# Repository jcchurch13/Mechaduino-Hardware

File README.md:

Engineers use servo motors to achieve the precision motion required in applications such as robotics, automation, and CNC manufacturing. Like RC servos, industrial servos actively correct for external disturbances. Unlike RC servos, industrial servos can provide very accurate motion, and often support advanced motion control modes. Unfortunately the cost of industrial servos is prohibitive to the individual maker (thousands of dollars per motor).

We've been developing an affordable open-source industrial servo motor, opening the door to sophisticated mechatronics applications. Our design leverages the low cost of mass produced stepper motors. We are able to achieve very high resolution via 14b encoder feedback (after calibration routine!).

## Project Goals

 - Position, velocity, torque loops
 - Step & direction inputs for drop-in compatibility with stepper motors / step stick
 - I2c, serial inputs
 - Customizable/open source with access to internal variables
 - Transparent and user-definable control algorithms (commercial servos often lack this)
 - Arduino compatible with easy to use interface
 - High resolution pointing (sub 0.1 degree)
 - Low cost (should not be a huge leap from stepper + stepstick cost)
 - Serial interfaces for inter-motor communication
 - On-board processor allows for stand alone for simple applications
 - Adjustable commutation profiles
 - PID auto tuning
 - Anti-cogging capable
 - Open to customization. Outside of our firmware, we see Mechaduino as a very useful hardware package. If you would like to use the stepper motor in open loop mode w/ encoder to verify location, you can do that.

## Strategy

An industrial servo motor can be broken down into four main components (below). First we looked at each of these components and tried to piece together an affordable breadboard-level prototype. After some experimentation, we were able to distill out a working lineup of components. From there, we've been iterating on our design, working out all the kinks, and tuning the control loops. It's starting to come together!

...Back to those four main components:

1. The actual motor, usually of the brushless dc variety. When you look at industrial servo motors, a big chunk of the cost is the motor itself. They are often custom built, or at least built in limited quantities, which means $$$. Watt for watt, I'd guess that a mass produced NEMA 17 or NEMA 23 stepper motor is between a tenth and a hundredth the cost of the BDC motors used in industrial servos. Although their design is optimized for "stepping," stepper motors are really just 50-pole brushless dc motors. They can be controlled exactly like a more traditional 3 phase BDC motor with more poles. So that's the plan. It's working!

2. A sensor for feedback, usually an encoder. Optical encoders are pretty standard, but get quite pricey if you want high resolution and/or absolute position information. We were intrigued by some of the cheap, high resolution magnetic encoders offered by vendors like AMS. It turns out that although they claim 12 and 14 bit resolutions (that's 0.09 and 0.02 degrees respectively), they suffer from non-linearities on the order of a degree or so! However, we found that this non-linearity is very repeatable, and we were able to develop a quick, self contained (on motor) calibration routine that restores resolution to better than 0.1 degrees. (More on this later. This was a significant design effort and is worthy of its own build log!)

3. Drive circuitry/power electronics to excite the motor windings. Many industrial servos use discrete H bridges. Each phase requires it's own H bridge ( for a two phase motor... half bridges for each in a three phase motor), which consists of at least 4 if not 8 (...including freewheeling diodes) discrete switching devices. Throw in gate drive circuitry, and things start to get expensive. We hoped to find a single-chip, integrated solution that would allow for current feedback, and we found just that in the A4954 dual full bridge PWM driver.

4. Control Electronics. Usually a microcontroller or FPGA. Early on, we decided that Arduino compatibility was a must in order to make the firmware as accessible as possible. We chose to use a SAMD21 ARM M0+ (Arduino Zero compatible) processor to balance cost and performance. Our breadboard prototype system verified that this processor was more than capable of executing the necessary algorithms.

### Application Examples:

 - [Fine, closed loop positioning for 3D printers](https://www.youtube.com/watch?v=T1HIWAiMrfY)
 - Fine pointing for optics (laser, telescope, camera gimbal)
 - Velocity loop for a record player
 - Force feedback/impedance control for robotics
 - Force feedback for gaming controllers
 - Adjustable mechanical impedance: virtual spring,mass,damper
 - Electrical gearing between two axes on a cnc machine, etc.
 - Haptics
 - Tele-operation
 - Gravity-cancellation (counter the gravitational torques on a robotic arm for example)
 - Load detection and characterization (simple case: use as a scale!)
 - Paper towel/tp dispenser
 - Variable load (brake)
 - Variable load (generator)
 - After market valve control (automate a garden hose, etc)

### Other Advantages:

- Finer resolution than stepper motors (0.02 degrees)
- True closed loop for disturbance rejection
- Lower power consumption: only uses power to fight disturbances. This in turn means higher peak torque.
- Absolute position control (not incremental). No need to home on power-on.

## License

All Mechaduino related materials are released under the
[Creative Commons Attribution Share-Alike 4.0 License](https://creativecommons.org/licenses/by-sa/4.0/)

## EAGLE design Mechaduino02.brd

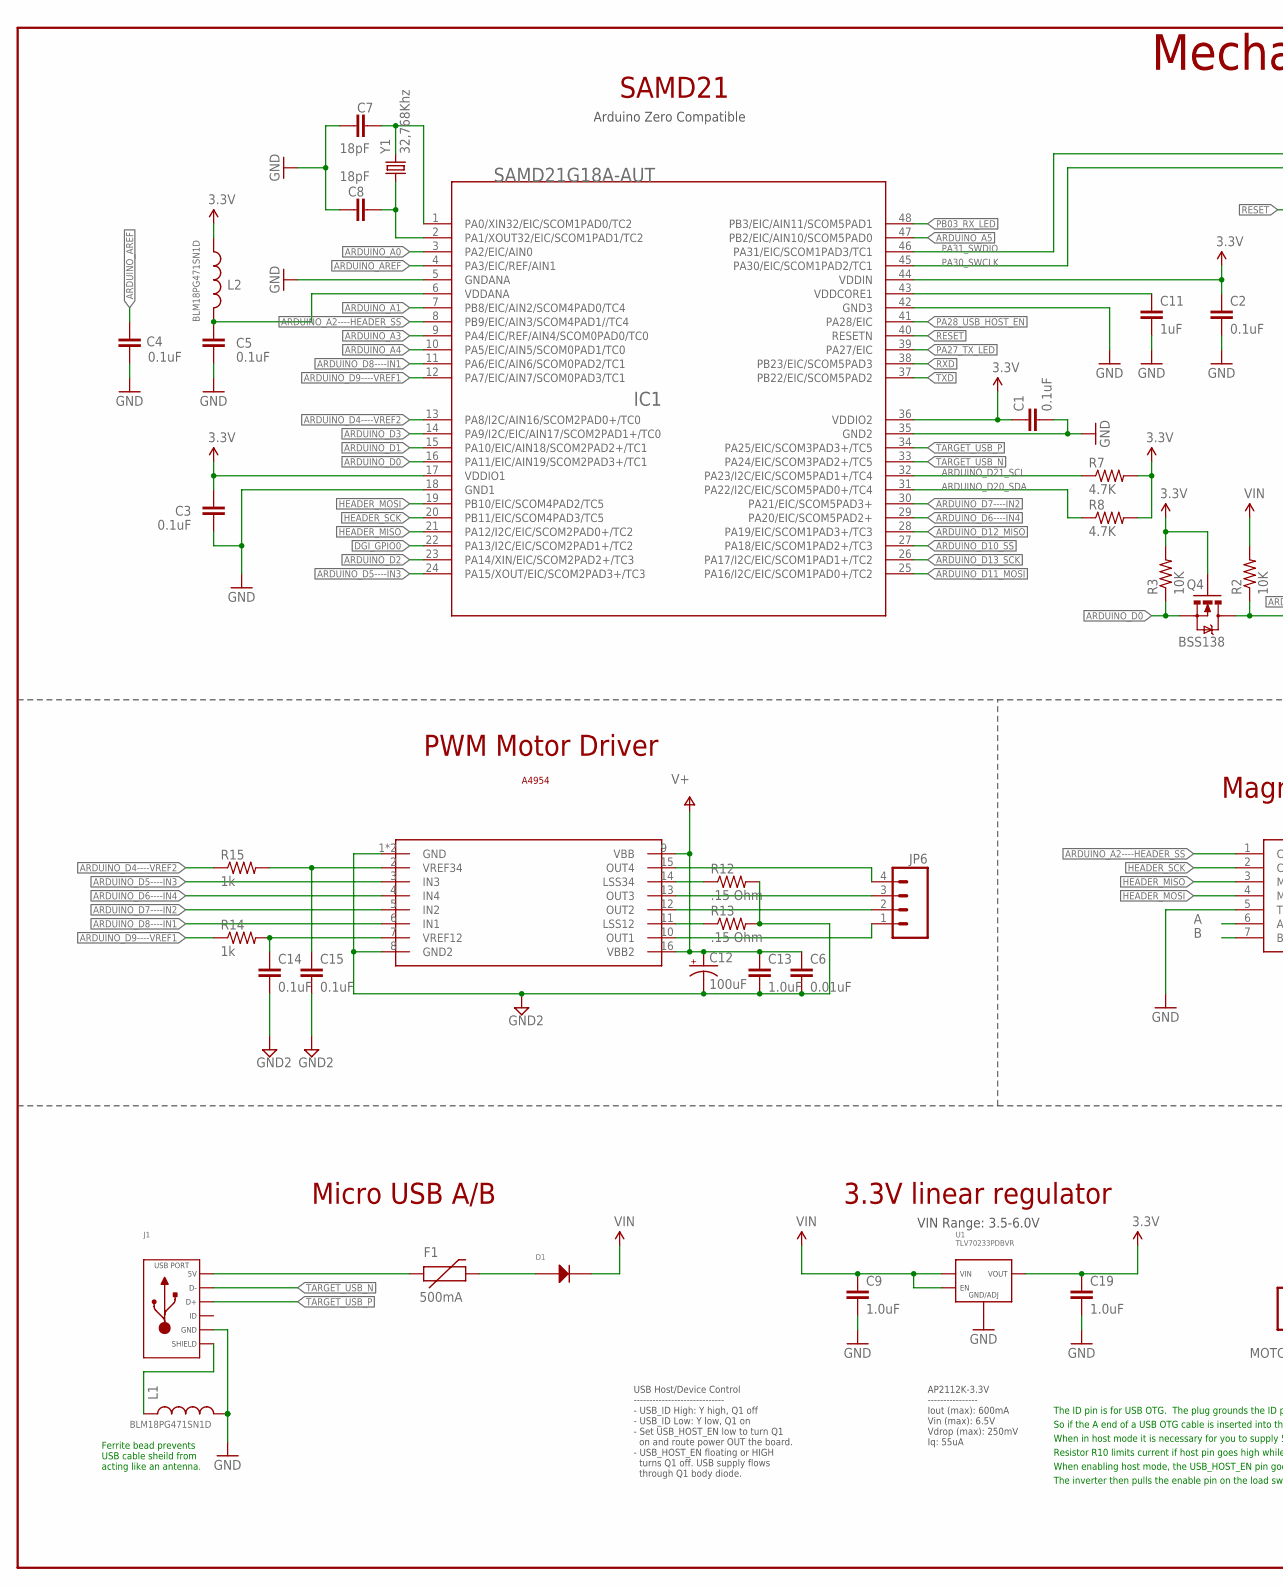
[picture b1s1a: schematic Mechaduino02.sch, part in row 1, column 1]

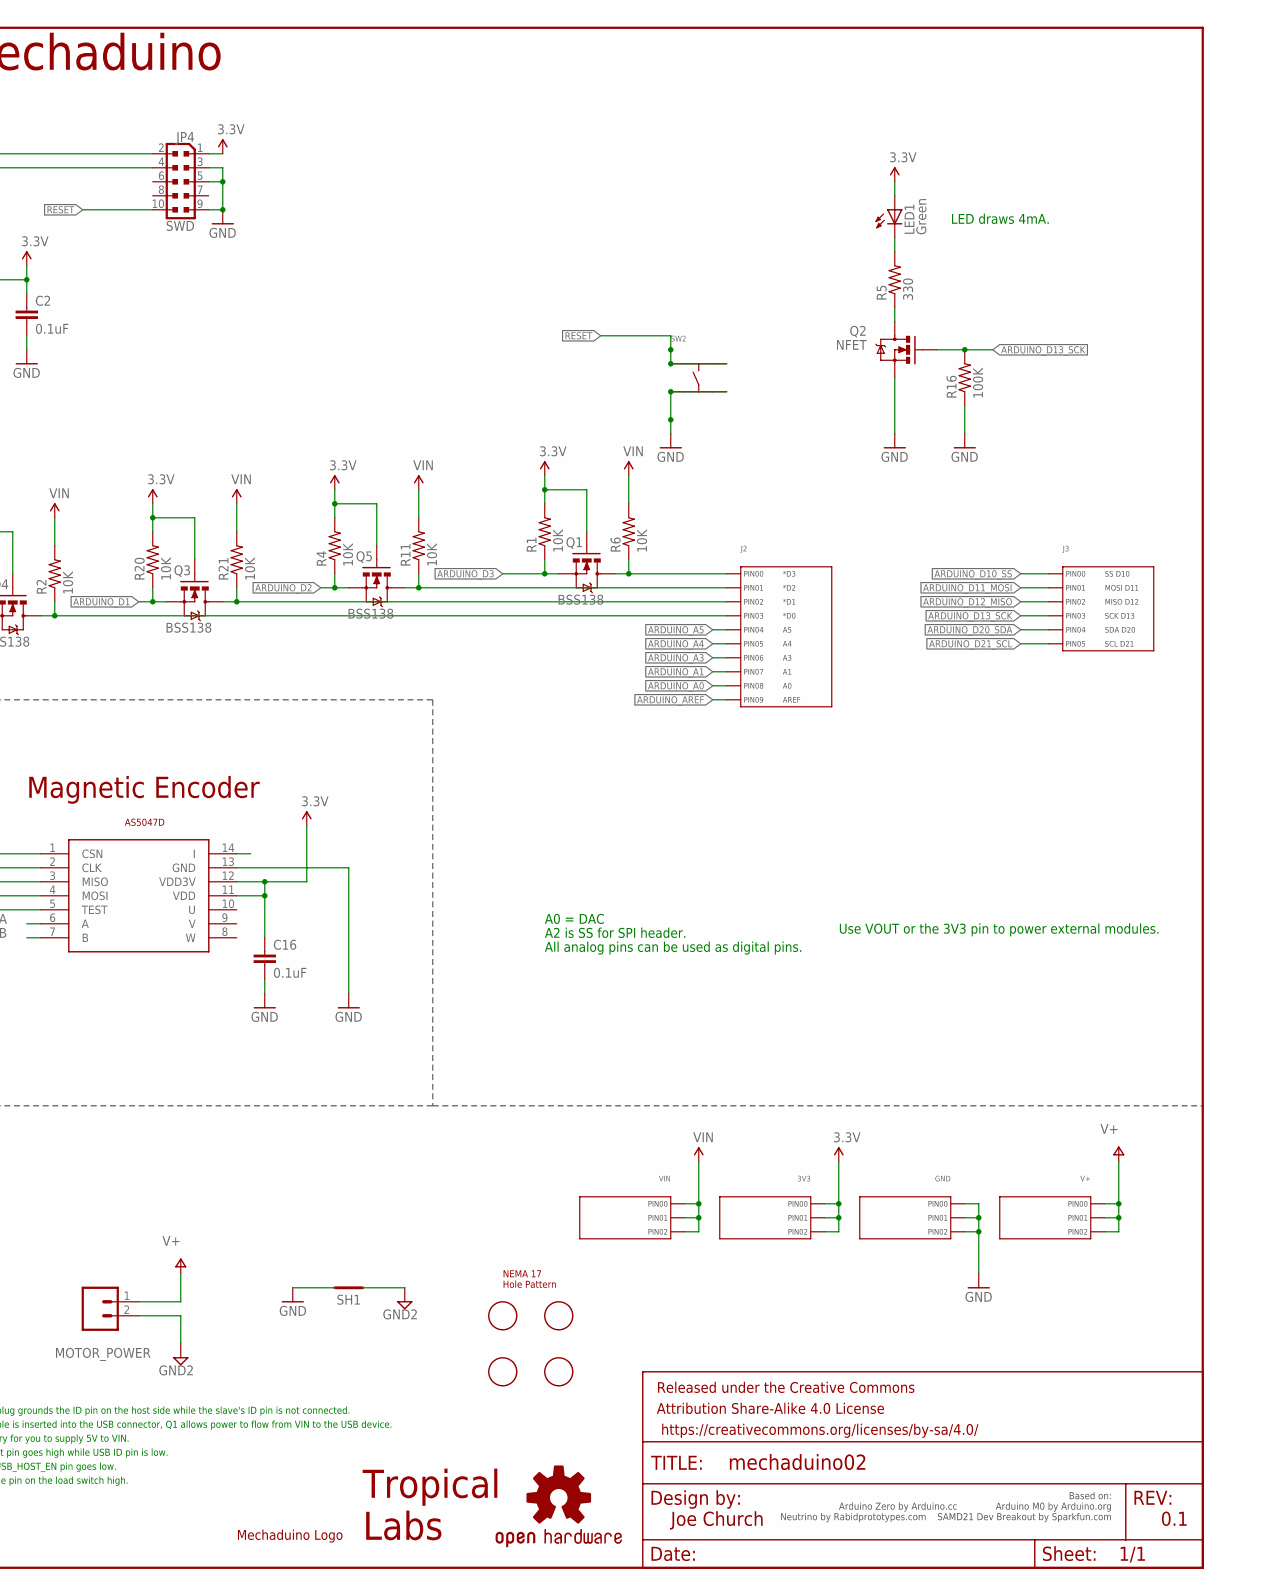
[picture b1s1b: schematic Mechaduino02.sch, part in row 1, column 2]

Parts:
3V3: HEADER_01X03_PTH_2.54MM; PTH_2.54MM_01X03
C1, C2, C3, C4, C5, C14, C15, C16: 0.1uF; 0402-CAP
C6: 0.01uF; 0603-CAP
C7, C8: 18pF; 0603-CAP
C9, C19: 1.0uF; 0402-CAP
C11: 1uF; 0402-CAP
C12: 100uF; PANASONIC_D
C13: 1.0uF; 0603-CAP
D1: DIODE_SOD-123; SOD-123
F1: 500mA; PTC-1206
FRAME1: FRAME-LEDGER; CREATIVE_COMMONS
GND: HEADER_01X03_PTH_2.54MM; PTH_2.54MM_01X03
IC1: SAMD21G18A-AUT; INTEGRATEDCIRCUITS_TQFP48-7X7
J1: USB_MICRO_RIGHT; MICROUSB-RIGHT
J2: HEADER_01X10_PTH_2.54MM; PTH_2.54MM_01X10
J3: HEADER_01X06_PTH_2.54MM; PTH_2.54MM_01X06
JP4: SWD; CONNETTORI_PINHEAD-2X5-P127
JP6: M04PTH; 1X04
L1, L2: BLM18PG471SN1D; 0603-TDK
LED1: Green; CHIPLED_0805
LOGO4: OSHW-LOGOMOD; OSHW_LOGO_COPPER_MOD
MOTOR_POWER: M025MM; SCREWTERMINAL-5MM-2
Q1, Q3, Q4, Q5: BSS138; SOT23-3
Q2: NFET; SOT323
R1, R2, R3, R4, R6, R11, R20, R21: 10K; R0402-VISHAY
R5: 330; R0402-VISHAY
R7, R8: 4.7K; R0402-VISHAY
R12, R13: .15 Ohm; R1206
R14, R15: 1k; R0402-VISHAY
R16: 100K; R0402-VISHAY
SH1: SHORT-HA5; SHORT_ALL-50
SW2: TACT_4.2MM; TACT4.2MM
U1: TLV70233PDBVR; SOT-23-5
U$1: AVAGO_DRIVERTHERM; TSSOP16_THERM
U$2: NEMA17_HOLE_PATTERNNEW; NEMA17_HOLE_PATTERN_2
U$3: TROPICAL_LABS_LOGO_1LOGO3; LOGO3
U$4: AS5047D; TSSOP14
U$5: MECHADUINO_LOGO
V+: HEADER_01X03_PTH_2.54MM; PTH_2.54MM_01X03
VIN: HEADER_01X03_PTH_2.54MM; PTH_2.54MM_01X03
Y1: 32,768Khz; CRYSTAL-SMD-2.0X1.2

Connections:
3.3V: 3V3.P$1 (PIN0), 3V3.P$2 (PIN1), 3V3.P$3 (PIN2), C1.1, C2.1, C3.2, C16.1, C19.1, IC1.17 (VDDIO1), IC1.36 (VDDIO2), IC1.44 (VDDIN), JP4.1, L2.1, LED1.A, Q1.1 (G), Q3.1 (G), Q4.1 (G), Q5.1 (G), R1.2, R3.2, R4.2, R7.2, R8.2, R20.2, U1.P$5 (VOUT), U$4.11 (VDD), U$4.12 (VDD3V)
A: U$4.6 (A)
ARDUINO_A0: IC1.3 (PA2/EIC/AIN0), J2.P$9 (PIN8)
ARDUINO_A1: IC1.7 (PB8/EIC/AIN2/SCOM4PAD0/TC4), J2.P$8 (PIN7)
ARDUINO_A2----HEADER_SS: IC1.8 (PB9/EIC/AIN3/SCOM4PAD1//TC4), U$4.1 (CSN)
ARDUINO_A3: IC1.9 (PA4/EIC/REF/AIN4/SCOM0PAD0/TC0), J2.P$7 (PIN6)
ARDUINO_A4: IC1.10 (PA5/EIC/AIN5/SCOM0PAD1/TC0), J2.P$6 (PIN5)
ARDUINO_A5: IC1.47 (PB2/EIC/AIN10/SCOM5PAD0), J2.P$5 (PIN4)
ARDUINO_AREF: C4.1, IC1.4 (PA3/EIC/REF/AIN1), J2.P$10 (PIN9)
ARDUINO_D0: IC1.16 (PA11/EIC/AIN19/SCOM2PAD3+/TC1), Q4.2 (S), R3.1
ARDUINO_D1: IC1.15 (PA10/EIC/AIN18/SCOM2PAD2+/TC1), Q3.2 (S), R20.1
ARDUINO_D2: IC1.23 (PA14/XIN/EIC/SCOM2PAD2+/TC3), Q5.2 (S), R4.1
ARDUINO_D3: IC1.14 (PA9/I2C/EIC/AIN17/SCOM2PAD1+/TC0), Q1.2 (S), R1.1
ARDUINO_D4----VREF2: IC1.13 (PA8/I2C/AIN16/SCOM2PAD0+/TC0), R15.1
ARDUINO_D5----IN3: IC1.24 (PA15/XOUT/EIC/SCOM2PAD3+/TC3), U$1.3 (IN3)
ARDUINO_D6----IN4: IC1.29 (PA20/EIC/SCOM5PAD2+), U$1.4 (IN4)
ARDUINO_D7----IN2: IC1.30 (PA21/EIC/SCOM5PAD3+), U$1.5 (IN2)
ARDUINO_D8----IN1: IC1.11 (PA6/EIC/AIN6/SCOM0PAD2/TC1), U$1.6 (IN1)
ARDUINO_D9----VREF1: IC1.12 (PA7/EIC/AIN7/SCOM0PAD3/TC1), R14.1
ARDUINO_D10_SS: IC1.27 (PA18/EIC/SCOM1PAD2+/TC3), J3.P$1 (PIN0)
ARDUINO_D11_MOSI: IC1.25 (PA16/I2C/EIC/SCOM1PAD0+/TC2), J3.P$2 (PIN1)
ARDUINO_D12_MISO: IC1.28 (PA19/EIC/SCOM1PAD3+/TC3), J3.P$3 (PIN2)
ARDUINO_D13_SCK: IC1.26 (PA17/I2C/EIC/SCOM1PAD1+/TC2), J3.P$4 (PIN3), Q2.1 (G), R16.2
ARDUINO_D20_SDA: IC1.31 (PA22/I2C/EIC/SCOM5PAD0+/TC4), J3.P$5 (PIN4), R8.1
ARDUINO_D21_SCL: IC1.32 (PA23/I2C/EIC/SCOM5PAD1+/TC4), J3.P$6 (PIN5), R7.1
B: U$4.7 (B)
DGI_GPIO0: IC1.22 (PA13/I2C/EIC/SCOM2PAD1+/TC2)
GND: C1.2, C2.2, C3.1, C4.2, C5.2, C7.1, C8.1, C9.2, C11.2, C16.2, C19.2, GND.P$1 (PIN0), GND.P$2 (PIN1), GND.P$3 (PIN2), IC1.5 (GNDANA), IC1.18 (GND1), IC1.35 (GND2), IC1.42 (GND3), J1.5 (GND), JP4.3, JP4.5, JP4.9, L1.2, Q2.2 (S), R16.1, SH1.2, SW2.P$3, SW2.P$4, U1.P$2 (GND/ADJ), U$4.5 (TEST), U$4.13 (GND)
GND2: C6.2, C12.-, C13.2, C14.2, C15.2, MOTOR_POWER.2, R12.2, R13.2, SH1.1, U$1.1 (GND), U$1.8 (GND2), U$1.P$1 (GND)
HEADER_MISO: IC1.21 (PA12/I2C/EIC/SCOM2PAD0+/TC2), U$4.3 (MISO)
HEADER_MOSI: IC1.19 (PB10/EIC/SCOM4PAD2/TC5), U$4.4 (MOSI)
HEADER_SCK: IC1.20 (PB11/EIC/SCOM4PAD3/TC5), U$4.2 (CLK)
HV1: J2.P$3 (PIN2), Q3.3 (D), R21.1
HV2: J2.P$4 (PIN3), Q4.3 (D), R2.1
HV3: J2.P$2 (PIN1), Q5.3 (D), R11.1
HV4: J2.P$1 (PIN0), Q1.3 (D), R6.1
I: U$4.14 (I)
unnamed: LED1.C, R5.2
unnamed: R12.1, U$1.14 (LSS34)
unnamed: Q2.3 (D), R5.1
unnamed: R13.1, U$1.11 (LSS12)
unnamed: C15.1, R15.2, U$1.2 (VREF34)
unnamed: JP6.4, U$1.15 (OUT4)
unnamed: JP6.1, U$1.10 (OUT1)
unnamed: JP6.2, U$1.12 (OUT2)
unnamed: JP6.3, U$1.13 (OUT3)
unnamed: C14.1, R14.2, U$1.7 (VREF12)
unnamed: D1.ANODE, F1.2
unnamed: F1.1, J1.1 (5V)
PA00_XIN32: C7.2, IC1.1 (PA0/XIN32/EIC/SCOM1PAD0/TC2), Y1.2
PA01_XOUT32: C8.2, IC1.2 (PA1/XOUT32/EIC/SCOM1PAD1/TC2), Y1.1
PA27_TX_LED: IC1.39 (PA27/EIC)
PA28_USB_HOST_EN: IC1.41 (PA28/EIC)
PA30_SWCLK: IC1.45 (PA30/EIC/SCOM1PAD2/TC1), JP4.4
PA31_SWDIO: IC1.46 (PA31/EIC/SCOM1PAD3/TC1), JP4.2
PB03_RX_LED: IC1.48 (PB3/EIC/AIN11/SCOM5PAD1)
RESET: IC1.40 (RESETN), JP4.10, SW2.P$1, SW2.P$2
RXD: IC1.38 (PB23/EIC/SCOM5PAD3)
SHIELD: J1.S1 (SLD), J1.S2 (SLD), J1.S3 (SLD), J1.S4 (SLD), J1.S5 (SLD), J1.S6 (SLD), J1.S7 (SLD), J1.S8 (SLD), L1.1
TARGET_USB_N: IC1.33 (PA24/EIC/SCOM3PAD2+/TC5), J1.2 (D-)
TARGET_USB_P: IC1.34 (PA25/EIC/SCOM3PAD3+/TC5), J1.3 (D+)
TXD: IC1.37 (PB22/EIC/SCOM5PAD2)
V+: C6.1, C12.+, C13.1, MOTOR_POWER.1, U$1.9 (VBB), U$1.16 (VBB2), V+.P$1 (PIN0), V+.P$2 (PIN1), V+.P$3 (PIN2)
VDDANA: C5.1, IC1.6 (VDDANA), L2.2
VDDCORE: C11.1, IC1.43 (VDDCORE1)
VIN: C9.1, D1.CATHODE, R2.2, R6.2, R11.2, R21.2, U1.P$1 (VIN), U1.P$3 (EN), VIN.P$1 (PIN0), VIN.P$2 (PIN1), VIN.P$3 (PIN2)

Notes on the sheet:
A0 = DAC
All analog pins can be used as digital pins.
LED draws 4mA.
A2 is SS for SPI header.
Use VOUT or the 3V3 pin to power external modules.
Ferrite bead prevents USB cable sheild from acting like an antenna.
The ID pin is for USB OTG. The plug grounds the ID pin on the host side while the slave's ID pin is not connected.
So if the A end of a USB OTG cable is inserted into the USB connector, Q1 allows power to flow from VIN to the USB device.
3.3V linear regulator
When in host mode it is necessary for you to supply 5V to VIN.
When enabling host mode, the USB_HOST_EN pin goes low.
Resistor R10 limits current if host pin goes high while USB ID pin is low.
The inverter then pulls the enable pin on the load switch high.
Magnetic Encoder
SAMD21
PWM Motor Driver
VIN Range: 3.5-6.0V
AP2112K-3.3V ---------------- Iout (max): 600mA Vin (max): 6.5V Vdrop (max): 250mV Iq: 55uA
USB Host/Device Control ----------------------------- - USB_ID High: Y high, Q1 off - USB_ID Low: Y low, Q1 on - Set USB_HOST_EN low to turn Q1 on and route power OUT the board. - USB_HOST_EN floating or HIGH turns Q1 off. USB supply flows through Q1 body diode.
A4954
Micro USB A/B
Joe Church
Based on: Arduino Zero by Arduino.cc Arduino M0 by Arduino.org Neutrino by Rabidprototypes.com SAMD21 Dev Breakout by Sparkfun.com
0.1
Arduino Zero Compatible
Mechaduino

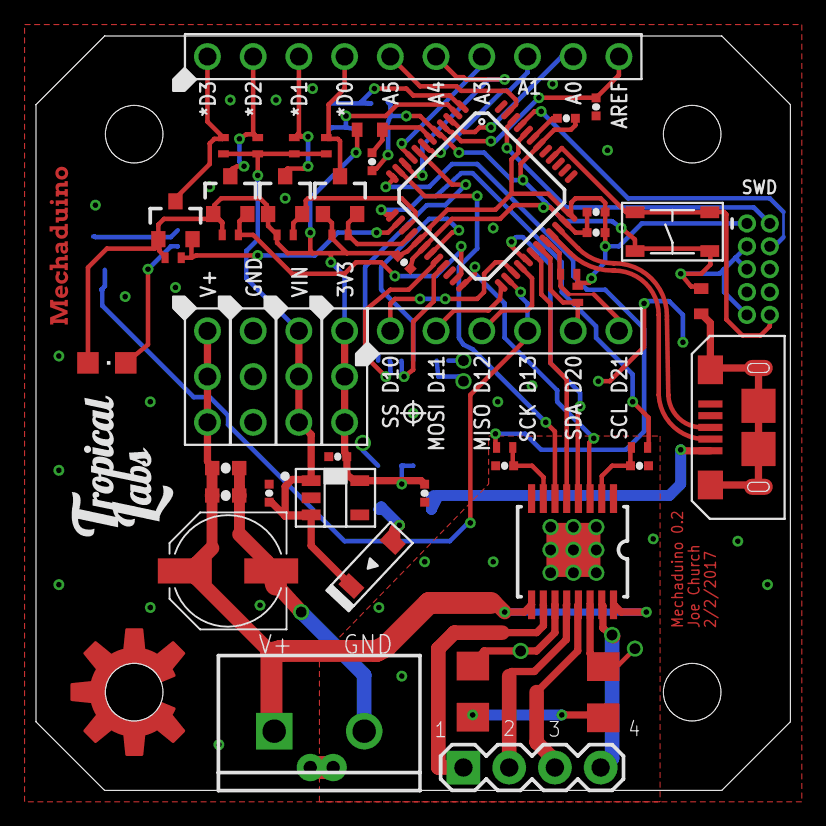
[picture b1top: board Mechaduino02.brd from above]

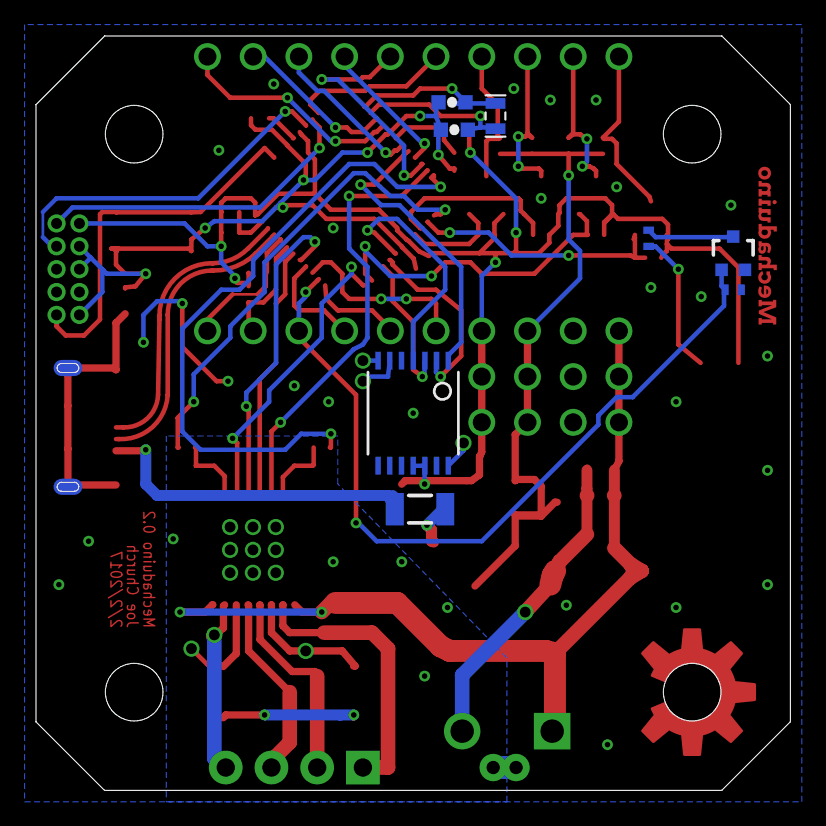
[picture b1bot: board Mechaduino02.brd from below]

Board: 2 copper layers, 41.9 x 41.9 mm, 64 parts (8 on the bottom side), 57 nets.

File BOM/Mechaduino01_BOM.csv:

Qty	Value	Device	Package	Parts	Description											
1	DIODESOD-523	SOD-523	D1	Diode												
4	HEADER_01X03_PTH_2.54MM	PTH_2.54MM_01X03	3V3	GND	V+	VIN	Library:	MF_Connectors								
1	HEADER_01X06_PTH_2.54MM	PTH_2.54MM_01X06	J3	Library:	MF_Connectors											
1	HEADER_01X10_PTH_2.54MM	PTH_2.54MM_01X10	J2	Library:	MF_Connectors											
1	M025MM	SCREWTERMINAL-5MM-2	MOTOR_POWER	"Standard 2-pin 0.1"" header. Use with"												
1	M04PTH	1X04	JP6	Header	4											
1	TACT_4.2MM	TACT4.2MM	SW2	Library:	MF_Switches											
1	USB_MICRO_RIGHT	MICROUSB-RIGHT	J1	Library:	MF_Connectors											
2	0.15	Ohm	R-US_R1206	R1206	R12	R13	RESISTOR	American	symbol							
1	0.01uF	CAP0402	0402-CAP	C6	Capacitor											
10	0.1uF	CAP0402	0402-CAP	C1	C2	C3	C4	C5	C9	C14	C15	C16	C19	Capacitor		
1	1.0uF	CAP0603	0603-CAP	C13	Capacitor											
2	10.0uF	CAP0402	0805-CAP	C10	C18	Capacitor										
2	100K	R-US_R0402-VISHAY	R0402-VISHAY	R1	R9	RESISTOR	American	symbol								
1	100k	R-US_R0402-VISHAY	R0402-VISHAY	R16	RESISTOR	American	symbol									
1	100uF	CAP_POLD	PANASONIC_D	C12	Capacitor	Polarized										
4	10K	R-US_R0402-VISHAY	R0402-VISHAY	R2	R3	R20	R21	RESISTOR	American	symbol						
2	1k	R-US_R0402-VISHAY	R0402-VISHAY	R14	R15	RESISTOR	American	symbol								
2	1uF	CAP0402	0402-CAP	C11	C17	Capacitor										
1	2.5A/30V	MOSFET-PCHANNELDMG2307L	SOT23-3	Q1	Generic	PMOSFET										
2	22pF	CAP0402	0402-CAP	C7	C8	Capacitor										
1	32	768Khz	CRYSTAL2012	CRYSTAL-SMD-2.0X1.2	Y1	Various	standard	crystals.	Proven	footprints.	Spark	Fun	Electronics	SKU	:	COM-00534
3	330	R-US_R0402-VISHAY	R0402-VISHAY	R5	R6	R10	RESISTOR	American	symbol							
2	4.7K	R-US_R0402-VISHAY	R0402-VISHAY	R7	R8	RESISTOR	American	symbol								
1	47K	47KOHM1/10W1%(0603)	0603-RES	R19	RES-07871											
1	500mA	PTCSMD	PTC-1206	F1	Resettable	Fuse	PTC									
1	74AHC1G125	74AHC1G125	SOT23-5	U3	Single	bus	buffer	gate	with	3-state	output					
1	AP2112K-3.3	AP2112K-3.3       	SOT23-5@1	IC2	AP2112K-3.3       	3.3V	LDO									
1	AS5047D	AS5047D	TSSOP14	U$4												
1	AVAGO_DRIVER	AVAGO_DRIVER	TSSOP16	U$1												
2	BLM18PG471SN1D	INDUCTOR0603-TDK	0603-TDK	L1	L2	Inductors										
2	BSS138	MOSFET-NCHANNELSMD	SOT23-3	Q3	Q4											
1	FRAME-LEDGER	FRAME-LEDGER	CREATIVE_COMMONS	FRAME1	Schematic	Frame										
1	Green	0044_KPT-2012YC	CHIPLED_0805	LED1	LED	YELLOW	-0	SMD	-0	805						
1	MECHADUINO_LOGO	MECHADUINO_LOGO	MECHADUINO_LOGO	U$5												
1	NEMA17_HOLE_PATTERN	NEMA17_HOLE_PATTERN	NEMA17_HOLE_PATTERN	U$2												
1	NFET	MOSFET-NCHANNEL2N7002PW	SOT323	Q2	Common	NMOSFET	Parts									
1	OSHW-LOGOL-COPPER	OSHW-LOGOL-COPPER	OSHW-LOGO-L_COPPER	LOGO4	Open	Source	Hardware	Logo								
1	SAMD21G18A-AUT	INTEGRATEDCIRCUITS_1792_SAMD21G18A-AUT	INTEGRATEDCIRCUITS_TQFP48-7X7	IC1	Atmel	D21	32bit	ARM	Cortex-M0	microcontroller	-0	48	PIN	TQFP		
1	SHORT-HA5	SHORT-HA5	SHORT_ALL-50	SH1	Short	between	two	nets								
1	SWD	CONNETTORI_0171_PH127-205DF055G00A	CONNETTORI_PINHEAD-2X5-P127	JP4	2x5	PASSO	1	27								
1	TROPICAL_LABS_LOGO_1LOGO3	TROPICAL_LABS_LOGO_1LOGO3	LOGO3	U$3

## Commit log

2016-03-24 :neckbeard: Added .gitattributes & .gitignore files
2016-03-24 copied from v 0.0
    baseline
2016-03-24 Swapped pins 2 and 4
2016-03-26 cleaned up
    including net labels
2016-03-26 Updated power supply
    Borrowed from sparkfun samd21 pro
2016-03-26 hardwired encoder, driver
2016-03-26 formatted and added license
2016-03-27 ready for layout
    ripped up old stuff, shrunk to 1.65" square from 1.7" and moved
    placement sensitive parts accordingly
2016-03-27 added level shifter
    on D0, D1
2016-03-31 cut corners
2016-03-31 cut corners...
    resaved
2016-04-02 replaced through hole passives with smd
2016-04-09 routed?
2016-04-09 fixed last unrouted
    also increased polygon isolate to 8 thou
2016-04-10 passes DRC
    with exception of some minor dimension, intentional overlap and stop
    mask errors
2016-04-12 reviewed
    updated graphics, checked stuff... done?
2016-04-19 Final
    ordered
2016-06-02 Created license file
2016-06-03 Added README and Images
2016-06-03 Made CSV openable via excel
2016-06-03 Removed Backup Files
2016-06-04 Moved Libraries to Library Folder
2016-06-04 Removed autorouter .job logs
2016-06-04 Moved and Renamed BOM Files :page_with_curl:
2016-06-04 Zipped Gerber Files :paperclip:
2016-06-24 Current sense
    changed Rsense from 0.25 ohm to 0.15 ohm
2016-08-09 Fix case sensitivity on 100k res
    Case sensitivity in BOM export causes 2 seperate entries in the BOM
    under the 100k resistors. Ks are mostly capitalized throughout the
    schematic, so corrected this one.
2016-08-09 100k to 100K
2016-08-11 changed BOM C10,C18
    from 0402 to 0805 (matched board now)
2016-08-14 Fixed AP2112K-3.3
2016-08-24 Gerbers updated
2016-08-24 updated Gerber .zip
2016-09-26 Updated rSense
2017-01-27 minor change to as5047 power circuit
2017-01-27 added third level shifter (same as others)
2017-01-28 nothing new
2017-01-29 fixed library stuff
2017-01-29 fixed thermal and a4954 clearance
2017-02-01 moved IO headers down 0.01
2017-02-01 moved things around
2017-02-03 commit after rollback issues
2017-02-03 almost completely routed
2017-02-03 passes DRC
    should still double check
2017-02-03 saved everything
2017-02-03 minor fixes
2017-02-03 moved button
2017-02-03 updated caps
2017-02-03 reday to order
2017-02-03 fixed file names, also silkscreen for *D3,*D2
2017-02-03 fixed bom
2017-02-03 via stitching
    cleaned up ground pours
2017-02-03 fixed xtal caps and power caps to 0603
2017-02-03 moved vias away from header
2017-03-19 a couple more changes
    fixed cap sizes? changed some text under regulator
2017-04-28 fixed BOM, header
2017-04-28 removed 0.1 files
2017-05-04 updated schematic text
2017-05-04 re-exported image, libraries
2017-05-04 updated image

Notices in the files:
parts and their libraries:
SparkFun-Connectors: Licensing: Creative Commons ShareAlike 4.0 International - https://creativecommons.org/licenses/by-sa/4.0
